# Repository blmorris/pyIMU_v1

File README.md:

pyskin-IMU
==========

Directory pyIMU contains an IMU skin for the pyboard, providing the MPU9150 accelerometer / gyro / magnetometer and the BMP180 barometric altimeter.

The eagle library pyIMU-03.lbr provides all components and symbols used in this board and schematic.

UPDATE: pyIMU-GPS contains an updated version of the original pyIMU board with a fully integrated GPS receiver module and interface circuitry for monitoring current draw and voltage on a Li-polymer battery pack.

Several device packages have been modified from the originals provided by Sparkfun and the standard Eagle libraries; this is to eliminate design rule check errors and ensure that there is soldermask between the pins on the fine-pitch (0.5mm) components.

The project uses the SSC-EAGLE-2Lyr_v1.0.0.3.dru design rule file; this is a design rule set for 2-layer boards provided by Sunstone Circuits: http://www.sunstone.com/news-resources/cad-tools/eagle

The current project should not generate any errors when run against this DRU file.

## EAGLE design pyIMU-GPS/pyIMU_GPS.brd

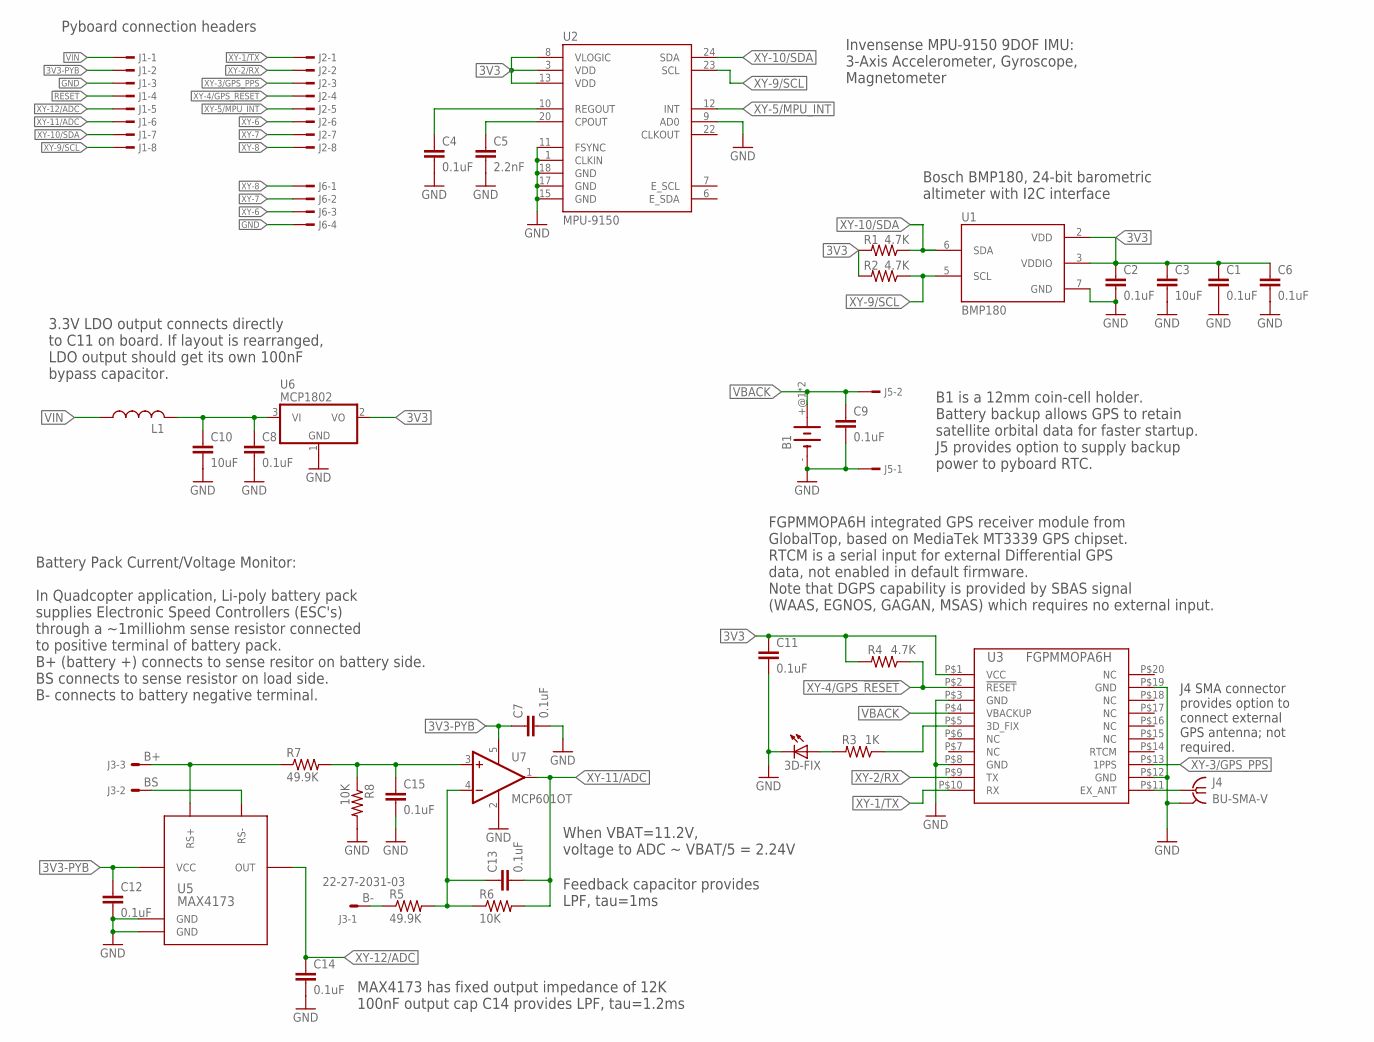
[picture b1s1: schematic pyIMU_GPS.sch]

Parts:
3D-FIX: LEDCHIPLED_0805; CHIPLED_0805
B1: BATT_HOLDERK3000; KEYSTONE-3000
C1, C2, C4, C6, C7, C8, C9, C11, C12, C13, C14, C15: 0.1uF; C0603K
C3, C10: 10uF; C0805K
C5: 2.2nF; C0603K
J1, J2: TSW-108-02-S-S-MOD
J3: 22-27-2031-03; 6410-03
J4: BU-SMA-V
J5: TSW-102-02-S-S
J6: TSW-104-02-S-S; TSW-104-S-S-MOD
L1: L-USL3216C; L3216C
R1, R2, R4: 4.7K; R0603
R3: 1K; R0603
R5, R7: 49.9K; R0805
R6, R8: 10K; R0805
U1: BMP180
U2: MPU-9150; QFN-24-NP
U3: FGPMMOPA6H
U5: MAX4173; SOT23-6L
U6: MCP1802; SOT23
U7: MCP601OT; SOT23-5

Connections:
3V3: C1.1, C2.1, C3.1, C6.1, C11.1, R1.2, R2.2, R4.2, U1.2 (VDD), U1.3 (VDDIO), U2.3 (VDD), U2.8 (VLOGIC), U2.13 (VDD), U3.P$1 (VCC), U6.2 (VO)
3V3-PYB: C7.1, C12.1, J1.2, U5.3 (VCC), U7.5 (V+)
!RESET: J1.4
B+: J3.3, R7.1, U5.4 (RS+)
B-: J3.1, R5.1
BS: J3.2, U5.5 (RS-)
GND: 3D-FIX.C, B1.-, C1.2, C2.2, C3.2, C4.2, C5.2, C6.2, C7.2, C8.2, C9.2, C10.2, C11.2, C12.2, C14.2, C15.2, J1.3, J4.2, J4.3 (2), J4.4 (2), J4.5 (2), J5.1, J6.4, R8.2, U1.7 (GND), U2.1 (CLKIN), U2.9 (AD0), U2.11 (FSYNC), U2.15 (GND), U2.17 (GND), U2.18 (GND), U3.P$3 (GND), U3.P$8 (GND), U3.P$12 (GND), U3.P$19 (GND), U5.1 (GND), U5.2 (GND), U6.1 (GND), U7.2 (V-)
unnamed: C4.1, U2.10 (REGOUT)
unnamed: C5.1, U2.20 (CPOUT)
unnamed: J4.1, U3.P$11 (EX_ANT)
unnamed: R3.1, U3.P$5 (3D_FIX)
unnamed: 3D-FIX.A, R3.2
unnamed: C15.1, R7.2, R8.1, U7.3 (+IN)
unnamed: C13.1, R5.2, R6.1, U7.4 (-IN)
unnamed: C8.1, C10.1, L1.2, U6.3 (VI)
VBACK: B1.+@1 (+), B1.+@2 (+), C9.1, J5.2, U3.P$4 (VBACKUP)
VIN: J1.1, L1.1
XY-1/TX: J2.1, U3.P$10 (RX)
XY-2/RX: J2.2, U3.P$9 (TX)
XY-3/GPS_PPS: J2.3, U3.P$13 (1PPS)
XY-4/GPS_!RESET: J2.4, R4.1, U3.P$2 (!RESET)
XY-5/MPU_INT: J2.5, U2.12 (INT)
XY-6: J2.6, J6.3
XY-7: J2.7, J6.2
XY-8: J2.8, J6.1
XY-9/SCL: J1.8, R2.1, U1.5 (SCL), U2.23 (SCL)
XY-10/SDA: J1.7, R1.1, U1.6 (SDA), U2.24 (SDA)
XY-11/ADC: C13.2, J1.6, R6.2, U7.1 (OUT)
XY-12/ADC: C14.1, J1.5, U5.6 (OUT)

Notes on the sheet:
FGPMMOPA6H integrated GPS receiver module from GlobalTop, based on MediaTek MT3339 GPS chipset. RTCM is a serial input for external Differential GPS data, not enabled in default firmware. Note that DGPS capability is provided by SBAS signal (WAAS, EGNOS, GAGAN, MSAS) which requires no external inpu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
When VBAT=11.2V, voltage to ADC ~ VBAT/5 = 2.24V
MAX4173 has fixed output impedance of 12K 100nF output cap C14 provides LPF, tau=1.2ms
Feedback capacitor provides LPF, tau=1ms
Battery Pack Current/Voltage Monitor: In Quadcopter application, Li-poly battery pack supplies Electronic Speed Controllers (ESC's) through a ~1milliohm sense resistor connected to positive terminal of battery pack. B+ (battery +) connects to sense resitor on battery side. BS connects to sense resi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
3.3V LDO output connects directly to C11 on board. If layout is rearranged, LDO output should get its own 100nF bypass capacitor.
Pyboard connection headers
B1 is a 12mm coin-cell holder. Battery backup allows GPS to retain satellite orbital data for faster startup. J5 provides option to supply backup power to pyboard RTC.
J4 SMA connector provides option to connect external GPS antenna; not required.
Bosch BMP180, 24-bit barometric altimeter with I2C interface
Invensense MPU-9150 9DOF IMU: 3-Axis Accelerometer, Gyroscope, Magnetometer

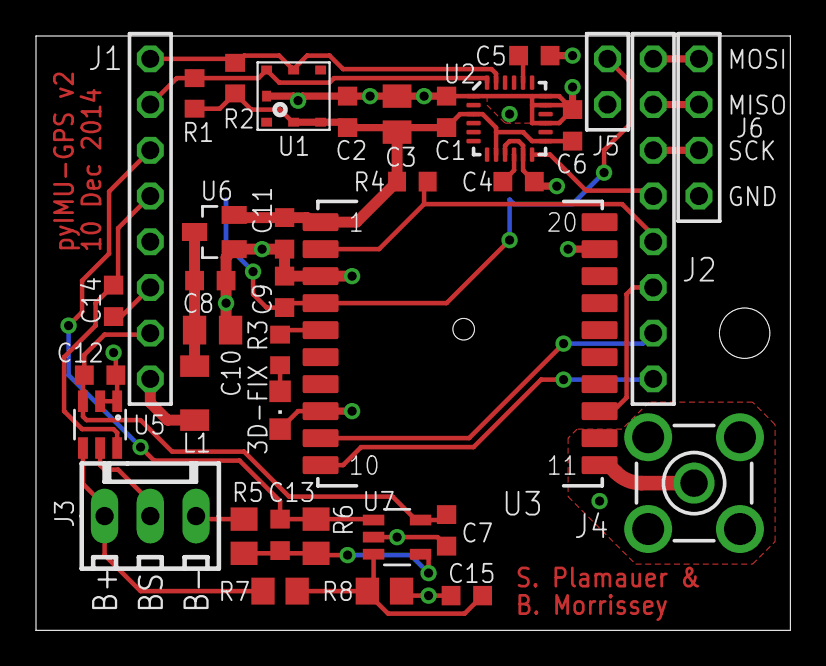
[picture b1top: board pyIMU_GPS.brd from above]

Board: 2 copper layers, 41.9 x 33.0 mm, 38 parts (1 on the bottom side), 28 nets.

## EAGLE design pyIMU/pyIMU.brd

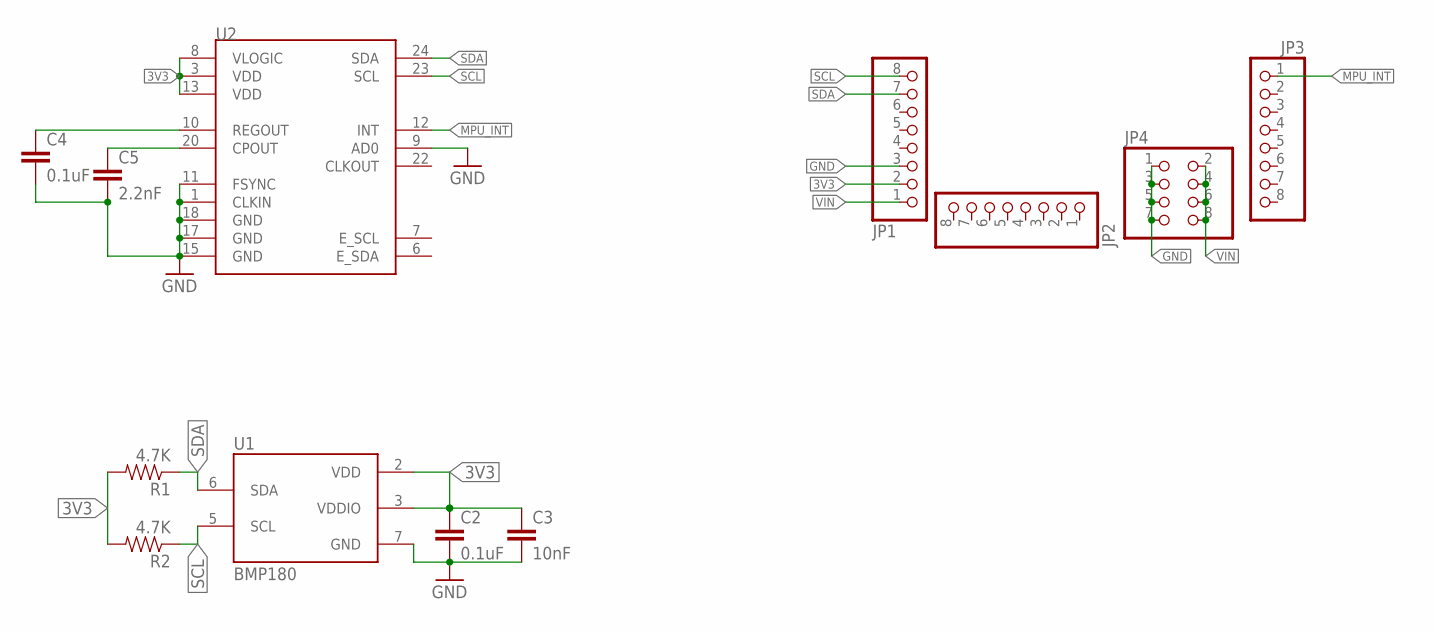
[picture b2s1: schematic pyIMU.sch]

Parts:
C2, C4: 0.1uF; 0603-CAP
C3: 10nF; 0603-CAP
C5: 2.2nF; 0603-CAP
JP1, JP2, JP3: PINHD-1X8; 1X08
JP4: PINHD-2X4; 2X04
R1, R2: 4.7K; 0603-RES
U1: BMP180
U2: MPU-9150QFN-24-NP; QFN-24-NP

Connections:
3V3: C2.1, C3.1, JP1.2, R1.2, R2.2, U1.2 (VDD), U1.3 (VDDIO), U2.3 (VDD), U2.8 (VLOGIC), U2.13 (VDD)
GND: C2.2, C3.2, C4.2, C5.2, JP1.3, JP4.1, JP4.3, JP4.5, JP4.7, U1.7 (GND), U2.1 (CLKIN), U2.9 (AD0), U2.11 (FSYNC), U2.15 (GND), U2.17 (GND), U2.18 (GND)
MPU_INT: JP3.1, U2.12 (INT)
unnamed: C4.1, U2.10 (REGOUT)
unnamed: C5.1, U2.20 (CPOUT)
SCL: JP1.8, R2.1, U1.5 (SCL), U2.23 (SCL)
SDA: JP1.7, R1.1, U1.6 (SDA), U2.24 (SDA)
VIN: JP1.1, JP4.2, JP4.4, JP4.6, JP4.8

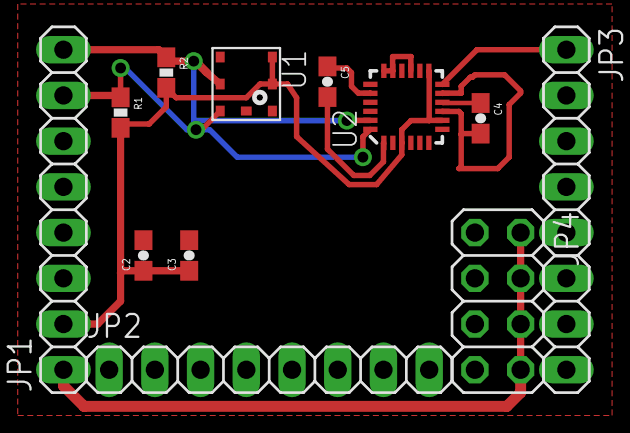
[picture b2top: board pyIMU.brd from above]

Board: 2 copper layers, 12 parts (0 on the bottom side), 8 nets.

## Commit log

2014-11-04 Update LICENSE
2014-11-04 initial
2014-11-04 added origin to LICENSE
2014-11-25 Initial commit of pyIMU v1
2014-11-25 Update README.md
    Add some information about the Eagle library and design rules used in the
2014-12-07 Added PDF's of the board and schematic for version 2 - preliminary desgins, subject to change.
2014-12-08 Commiting design files for GPS enabled version of pyIMU navigation board.
2014-12-08 Remove empty file from git index
2014-12-08 Update README with information about pyIMU-GPS
2014-12-09 Add mounting hole to board, move MPU_INT from XY8 to XY5, enlarge board slightly, shift GPS module and some other small changes
2014-12-10 Fix GPS module package so that all silkscreen markings are in top silkscreen layer Add a via in the SMA antenna ground pour. Move via in VBACK trace outside of battery holder outline to prevent possi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
2014-12-10 Update board and schematic PDF's
2014-12-10 Enlarge signal feed hole in center of SMA connector footprint. Available parts probably would not have fit if boards were run with previous footprint.
2014-12-10 Add gerber, excellon, and drill/photoplotter files To make a board use top, bot, oln, slk, smb, and smt gerber files along with drd excellon drill file. Other files just provide information about pro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

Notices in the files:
parts and their libraries:
SparkFun-Sensors: Licensing: Creative Commons ShareAlike 4.0 International - https://creativecommons.org/licenses/by-sa/4.0
